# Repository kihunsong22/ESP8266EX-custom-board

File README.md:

# ESP8266EX-custom-board
ESP8266EX test board with USB Type-C connector, 4MB flash and SMA connector for antenna.

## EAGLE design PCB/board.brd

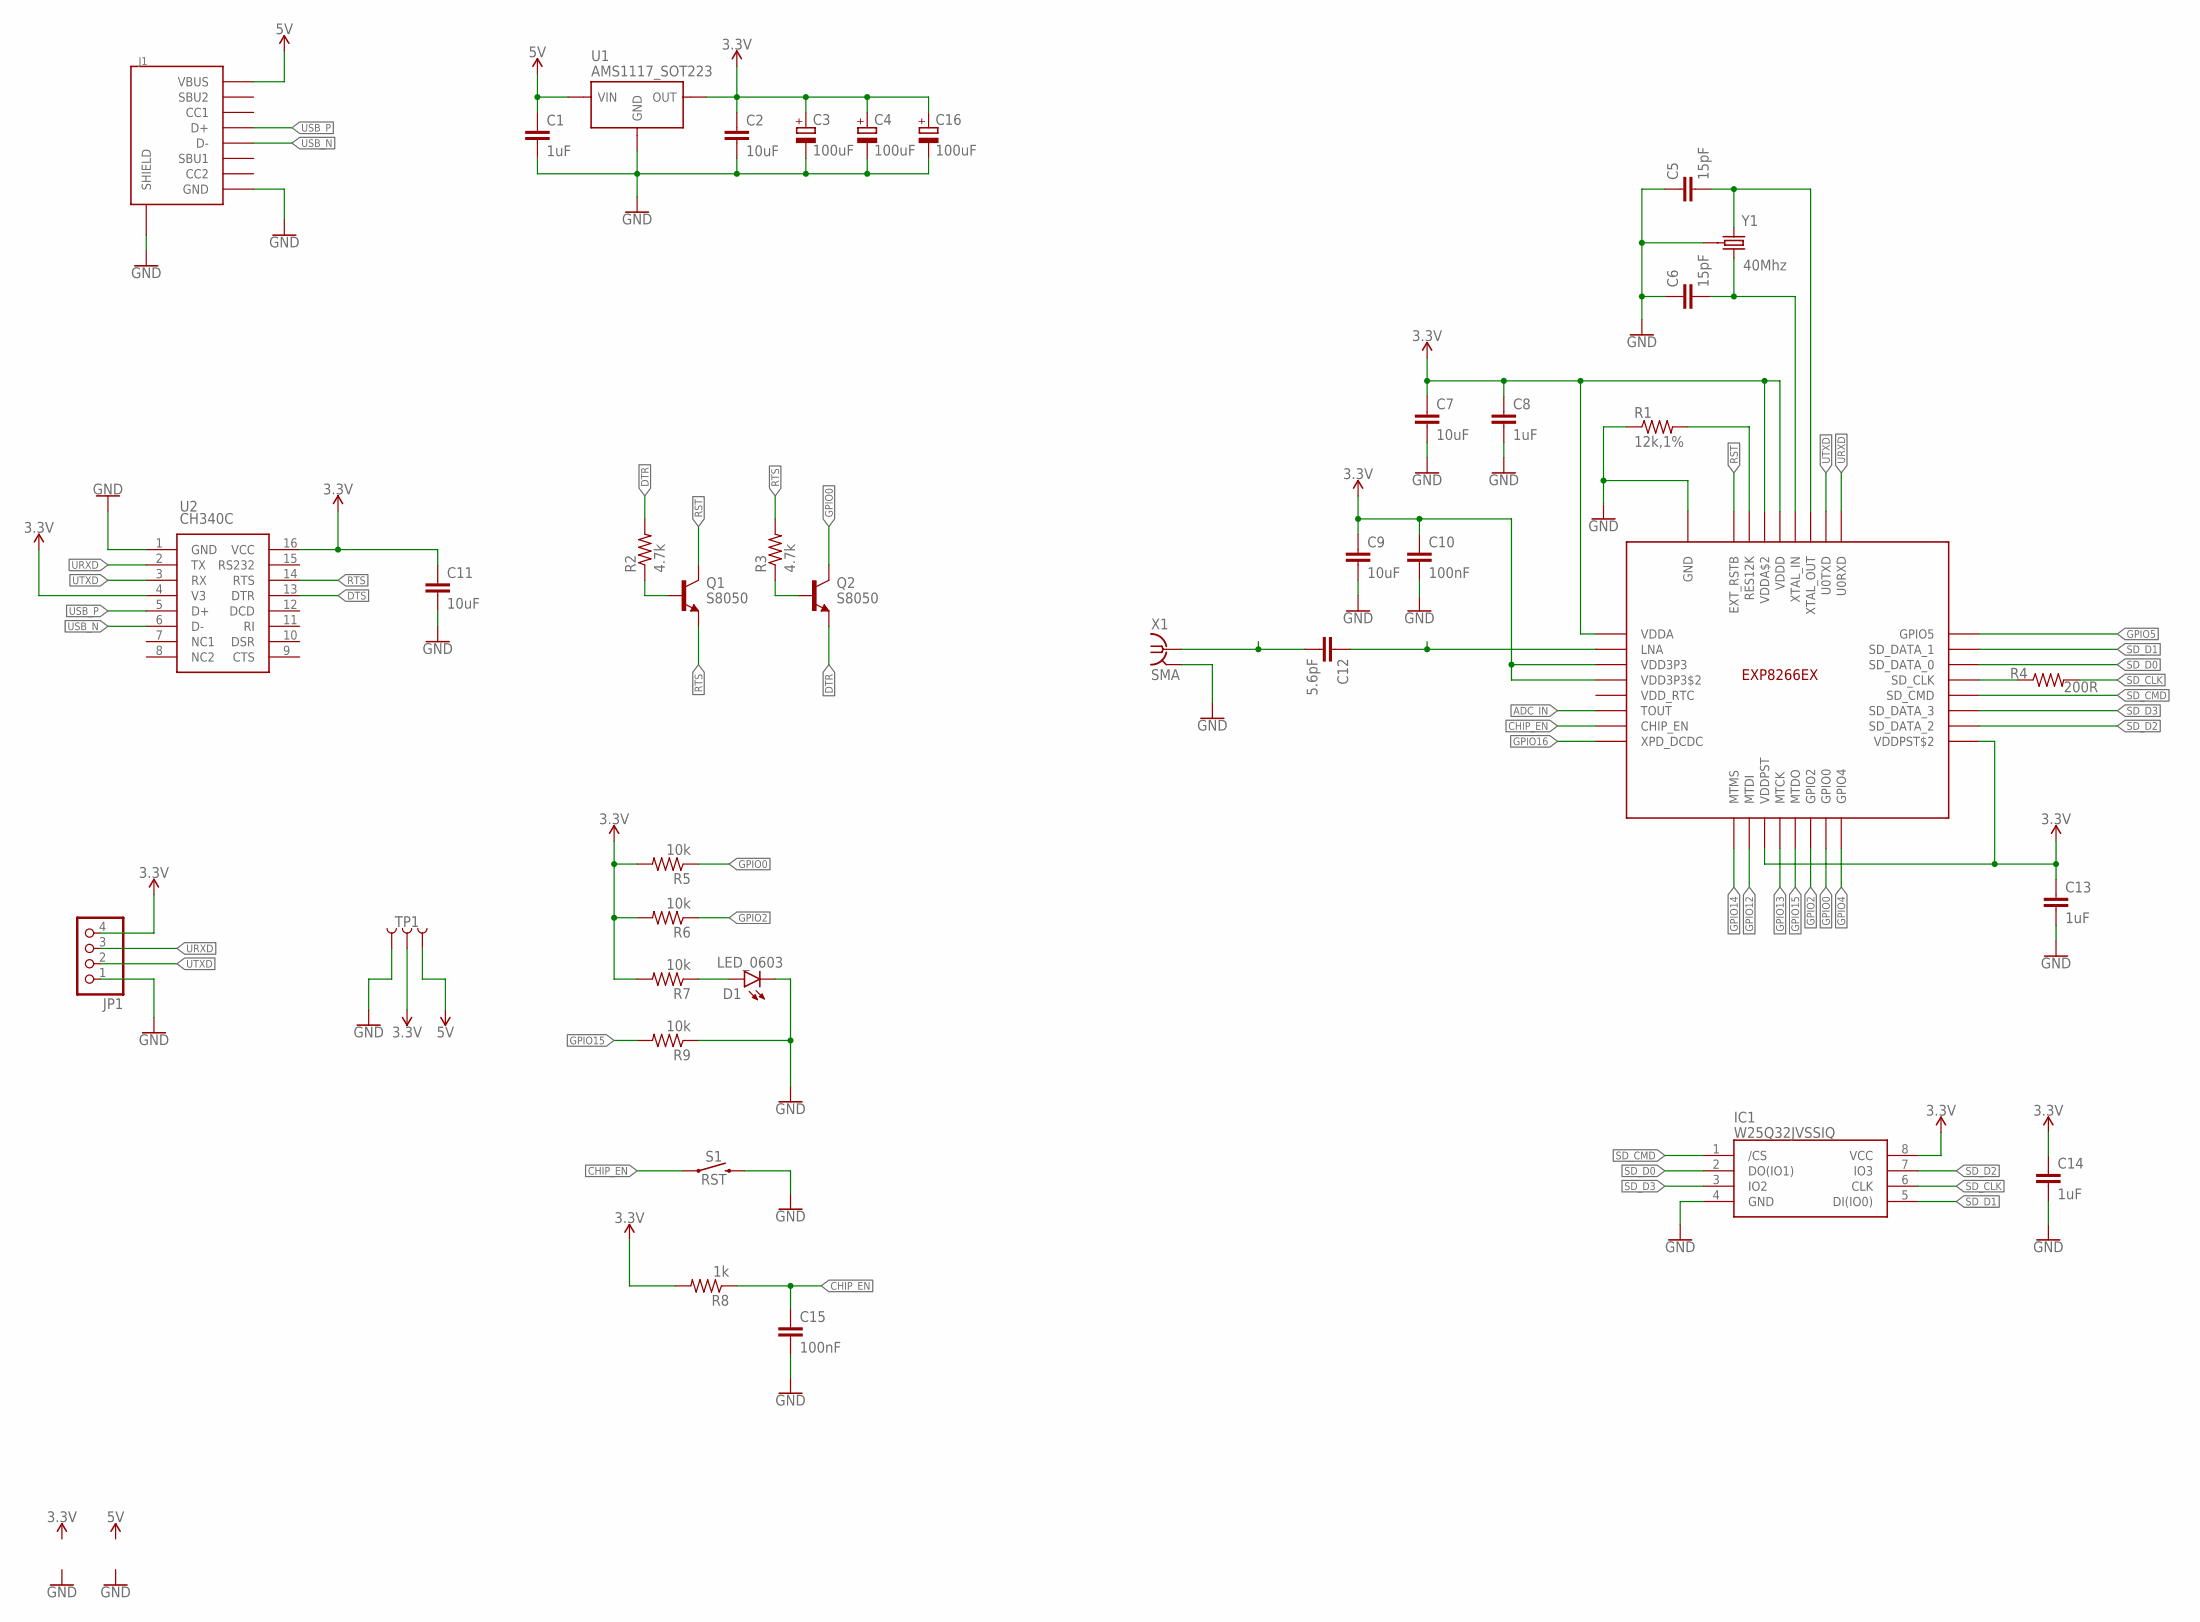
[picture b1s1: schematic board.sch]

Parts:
C1, C8, C13, C14: 1uF; C0402; LCSC C52923
C2, C7, C9, C11: 10uF; C0402; LCSC C15525
C3, C4, C16: 100uF; SMC_B; LCSC C16133
C5, C6: 15pF; C0402; LCSC C1548
C10, C15: 100nF; C0402; LCSC C1525
C12: 5.6pF; C0402; LCSC C318596
D1: LED_0603; LCSC C72038
IC1: W25Q32JVSSIQ; SOIC-8_208MIL; LCSC C179173
J1: USB-TYPE-C-31-M-12; LCSC C165948
JP1: PINHD-1X4/OCT; 1X04/OCT
Q1, Q2: S8050; SOT-23-3; LCSC C2146
R1: 12k,1%; R0402; LCSC C25752
R2, R3: 4.7k; R0402; LCSC C25900
R4: 200R; R0402; LCSC C25087
R5, R6, R7, R9: 10k; R0402; LCSC C25744
R8: 1k; R0402; LCSC C11702
S1: RST; TACTILE_SWITCH_SMD_6.0X3.5MM; LCSC C118141
TP1: TEST-POINT-3; PAD-3X-RECT-SILK
U1: AMS1117_SOT223; SOT-223; LCSC C6186
U2: CH340C; SOIC16; LCSC C14267
U3: ESP8266EX; LCSC C77967
X1: SMA; SMA-END-LAUNCH-2; LCSC C496550
Y1: 40Mhz; CRYSTAL-SMD-2X2.5MM; LCSC C284176

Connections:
3.3V: C2.1, C3.+, C4.+, C7.1, C8.1, C9.1, C10.1, C11.1, C13.1, C14.1, C16.+, IC1.8 (VCC), JP1.4, R5.2, R6.2, R7.2, R8.2, TP1.P$2 (2), U1.2 (OUT), U1.4 (OUT), U2.4 (V3), U2.16 (VCC), U3.VDD3P3, U3.VDD3P3$2, U3.VDDA, U3.VDDA$2, U3.VDDD, U3.VDDPST, U3.VDDPST$2
5V: C1.1, J1.VBUS1 (VBUS), J1.VBUS2 (VBUS), TP1.P$3 (3), U1.3 (VIN)
ADC_IN: U3.TOUT
CHIP_EN: C15.1, R8.1, S1.1, U3.CHIP_EN
DTR: Q2.2 (E), R2.2
DTS: U2.13 (DTR)
GND: C1.2, C2.2, C3.-, C4.-, C5.1, C6.1, C7.2, C8.2, C9.2, C10.2, C11.2, C13.2, C14.2, C15.2, C16.-, D1.C, IC1.4 (GND), J1.GND1 (GND), J1.GND2 (GND), J1.SHLD-B1 (SHIELD), J1.SHLD-B2 (SHIELD), J1.SHLD-B3 (SHIELD), J1.SHLD-B4 (SHIELD), J1.SHLD-T1 (SHIELD), J1.SHLD-T2 (SHIELD), J1.SHLD-T3 (SHIELD), J1.SHLD-T4 (SHIELD), JP1.1, R1.1, R9.1, S1.2, TP1.P$1 (1), U1.1 (GND), U2.1 (GND), U3.GND, X1.G@1 (2), X1.G@2 (2), X1.G@3 (2), X1.G@4 (2), Y1.P2 (GND), Y1.P4 (GND)
GPIO0: Q2.3 (C), R5.1, U3.GPIO0
GPIO2: R6.1, U3.GPIO2
GPIO4: U3.GPIO4
GPIO5: U3.GPOIO5 (GPIO5)
GPIO12: U3.MTDI
GPIO13: U3.MTCK
GPIO14: U3.MTMS
GPIO15: R9.2, U3.MTDO
GPIO16: U3.XPD_DCDC
unnamed: C6.2, U3.XTAL_IN, Y1.P3 (2)
unnamed: C5.2, U3.XTAL_OUT, Y1.P1 (1)
unnamed: R4.1, U3.SD_CLK
unnamed: R1.2, U3.RES12K
unnamed: C12.1, U3.LNA
unnamed: C12.2, X1.1
unnamed: D1.A, R7.1
unnamed: Q1.1 (B), R2.1
unnamed: Q2.1 (B), R3.1
RST: Q1.3 (C), U3.EXT_RSTB
RTS: Q1.2 (E), R3.2, U2.14 (RTS)
SD_CLK: IC1.6 (CLK), R4.2
SD_CMD: IC1.1 (/CS), U3.SD_CMD
SD_D0: IC1.2 (DO(IO1)), U3.SD_DATA_0
SD_D1: IC1.5 (DI(IO0)), U3.SD_DATA_1
SD_D2: IC1.7 (IO3), U3.SD_DATA_2
SD_D3: IC1.3 (IO2), U3.SD_DATA_3
URXD: JP1.3, U2.2 (TX), U3.U0RXD
USB_N: J1.A7 (D-), J1.B7 (D-), U2.6 (D-)
USB_P: J1.A6 (D+), J1.B6 (D+), U2.5 (D+)
UTXD: JP1.2, U2.3 (RX), U3.U0TXD

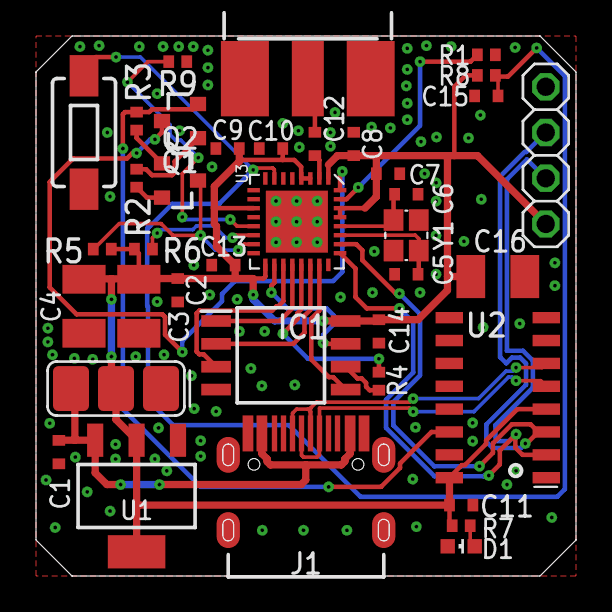
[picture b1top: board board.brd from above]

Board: 2 copper layers, 30.0 x 30.0 mm, 38 parts (0 on the bottom side), 29 nets.

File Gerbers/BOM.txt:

Part	Value	Device	Package	LCSC	
C1	1uF	C-NON-POLC0402	C0402	C52923	
C2	10uF	C-NON-POLC0402	C0402	C15525	
C3	100uF	C-POLARIZEDSMCB	SMC_B	C16133	
C4	100uF	C-POLARIZEDSMCB	SMC_B	C16133	
C5	15pF	C-NON-POLC0402	C0402	C1548	
C6	15pF	C-NON-POLC0402	C0402	C1548	
C7	10uF	C-NON-POLC0402	C0402	C15525	
C8	1uF	C-NON-POLC0402	C0402	C52923	
C9	10uF	C-NON-POLC0402	C0402	C15525	
C10	100nF	C-NON-POLC0402	C0402	C1525	
C11	10uF	C-NON-POLC0402	C0402	C15525	
C12	5.6pF	C-NON-POLC0402	C0402	C318596	
C13	1uF	C-NON-POLC0402	C0402	C52923	
C14	1uF	C-NON-POLC0402	C0402	C52923	
C15	100nF	C-NON-POLC0402	C0402	C1525	
C16	100uF	C-POLARIZEDSMCB	SMC_B	C16133	
D1	LED_0603	LED_0603	LED_0603	C72038	
IC1	W25Q32JVSSIQ	W25Q32JVSSIQ	SOIC-8_208MIL	C179173	
J1	USB-TYPE-C-31-M-12	USB-TYPE-C-31-M-12	USB-TYPE-C-31-M-12	C165948	
JP1	PINHD-1X4/OCT	1X04/OCT			
Q1	S8050	S8050	SOT-23-3	C2146	
Q2	S8050	S8050	SOT-23-3	C2146	
R1	"12k,"	1%	RR0402	R0402	C25752
R2	4.7k	RR0402	R0402	C25900	
R3	4.7k	RR0402	R0402	C25900	
R4	200R	RR0402	R0402	C25087	
R5	10k	RR0402	R0402	C25744	
R6	10k	RR0402	R0402	C25744	
R7	10k	RR0402	R0402	C25744	
R8	1k	RR0402	R0402	C11702	
S1	RST	SWITCH-SPST-SMD-6.0X3.5MM	TACTILE_SWITCH_SMD_6.0X3.5MM	C118141	
TP1	TEST-POINT-3	TEST-POINT-3	PAD-3X-RECT-SILK		
U1	AMS1117_SOT223	AMS1117_SOT223	SOT-223	C6186	
U2	CH340G	CH340G	SOIC16	C14267	
U3	ESP8266EX	ESP8266EX	ESP8266EX	C77967	
X1	SMA	SMA_END-LAUNCH-1	SMA-END-LAUNCH-2	C496550	
Y1	40Mhz	CRYSTAL-40MHZ_2520	CRYSTAL-SMD-2X2.5MM	C284176

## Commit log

2020-06-04 gitignore
2020-06-04 schematics
2020-06-04 added peripherals
2020-06-05 PCB layout
2020-06-05 added CH340
2020-06-05 first version, added gerbers and BOM
2020-06-12 CH340C
2020-06-17 CH340C - V3 pin wiring error
2020-06-17 GPIO15 pull-down
2020-06-18 pics
2020-07-02 library update

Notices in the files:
parts and their libraries:
SparkFun-PowerSymbols: Licensing: Creative Commons ShareAlike 4.0 International - https://creativecommons.org/licenses/by-sa/4.0
